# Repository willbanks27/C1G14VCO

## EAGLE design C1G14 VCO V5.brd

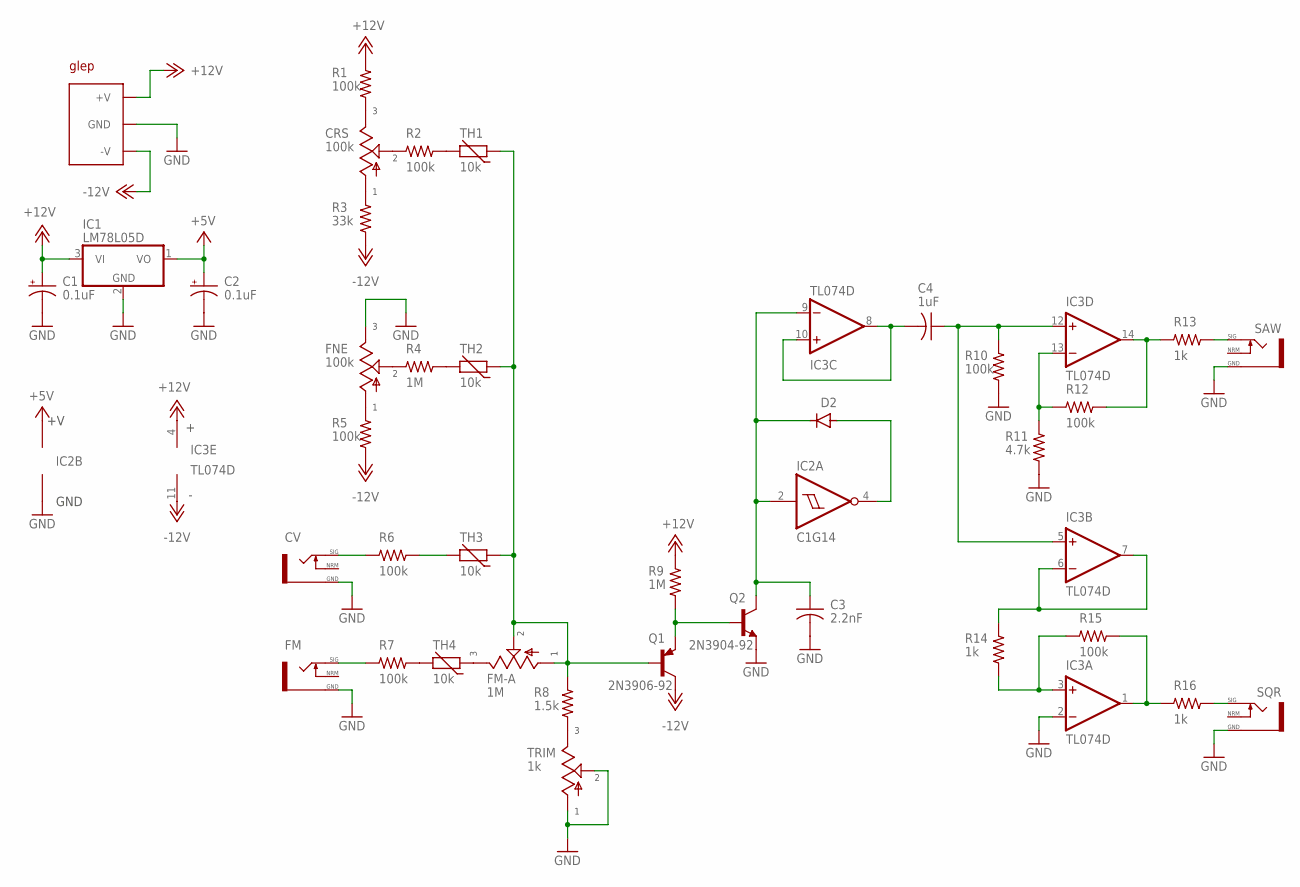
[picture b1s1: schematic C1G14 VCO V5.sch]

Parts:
C1, C2: 0.1uF; E025
C3: 2.2nF; C05
C4: 1uF; C05
CRS: 100k; HEADER
CV: MONOHDR; HEADER
D2: D-123; SOD-123
FM: MONOHDR; HEADER
FM-A: 1M; HEADER
FNE: 100k; HEADER
IC1: LM78L05D; LM78LXX
IC2: C1G14; SOT-23-5
IC3: TL074D; DIL14
Q1: 2N3906-92; TO92
Q2: 2N3904-92; TO92
R1, R2, R5, R6, R7, R10, R12, R15: 100k; R1206
R3: 33k; R1206
R4, R9: 1M; R1206
R8: 1.5k; R1206
R11: 4.7k; R1206
R13, R14, R16: 1k; R1206
SAW: MONOHDR; HEADER
SQR: MONOHDR; HEADER
TH1, TH2, TH3, TH4: 10k; TH025
TRIM: 1k; HEADER
U$1: 10PIN-PWR; 10PIN-HEADER
U$2: GLEP

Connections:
+5V: C2.+, IC1.1 (VO), IC2.5 (V+)
+12V: C1.+, IC1.3 (VI), IC3.4 (V+), R1.2, R9.2, U$1.9 (+V), U$1.10 (+V)
-12V: IC3.11 (V-), Q1.3 (C), R3.1, R5.1, U$1.1 (-V), U$1.2 (-V)
GND: C1.-, C2.-, C3.2, CV.GND (SLEEVE-GND), FM.GND (SLEEVE-GND), FNE.3, IC1.2 (GND), IC2.3 (GND), IC3.2 (INVERTING(-)), Q2.1 (E), R10.1, R11.1, SAW.GND (SLEEVE-GND), SQR.GND (SLEEVE-GND), TRIM.1, TRIM.2, U$1.3 (GND), U$1.4 (GND), U$1.5 (GND), U$1.6 (GND), U$1.7 (GND), U$1.8 (GND)
unnamed: CRS.2, R2.1
unnamed: C4.2, IC3.8 (OUT), IC3.10 (NON-INVERTING(+))
unnamed: CRS.1, R3.2
unnamed: R2.2, TH1.2
unnamed: CRS.3, R1.1
unnamed: FNE.2, R4.1
unnamed: R4.2, TH2.2
unnamed: FNE.1, R5.2
unnamed: IC3.6 (INVERTING(-)), IC3.7 (OUT), R14.2
unnamed: R6.2, TH3.2
unnamed: FM.TIP-SIG, R7.1
unnamed: R7.2, TH4.2
unnamed: FM-A.3, TH4.1
unnamed: R8.1, TRIM.3
unnamed: CV.TIP-SIG, R6.1
unnamed: Q1.1 (E), Q2.2 (B), R9.1
unnamed: C4.1, IC3.5 (NON-INVERTING(+)), IC3.12 (NON-INVERTING(+)), R10.2
unnamed: C3.1, D2.C, IC2.2 (A), IC3.9 (INVERTING(-)), Q2.3 (C)
unnamed: D2.A, IC2.4 (Y)
unnamed: IC3.13 (INVERTING(-)), R11.2, R12.1
unnamed: IC3.14 (OUT), R12.2, R13.1
unnamed: R13.2, SAW.TIP-SIG
unnamed: FM-A.1, FM-A.2, Q1.2 (B), R8.2, TH1.1, TH2.1, TH3.1
unnamed: IC3.3 (NON-INVERTING(+)), R14.1, R15.1
unnamed: IC3.1 (OUT), R15.2, R16.1
unnamed: R16.2, SQR.TIP-SIG

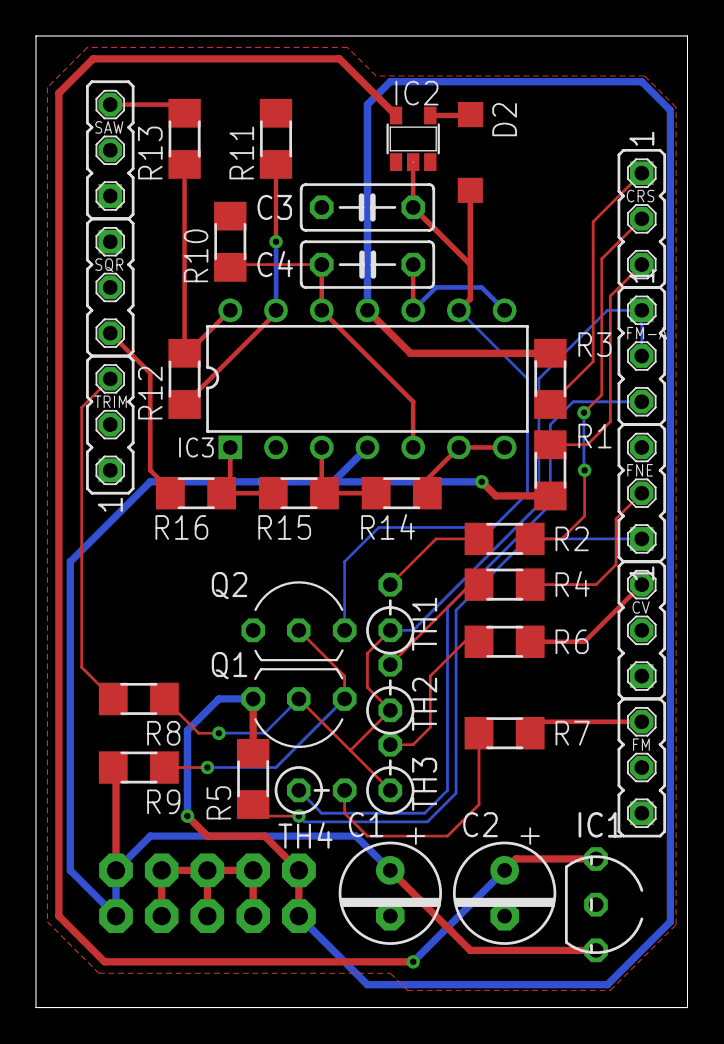
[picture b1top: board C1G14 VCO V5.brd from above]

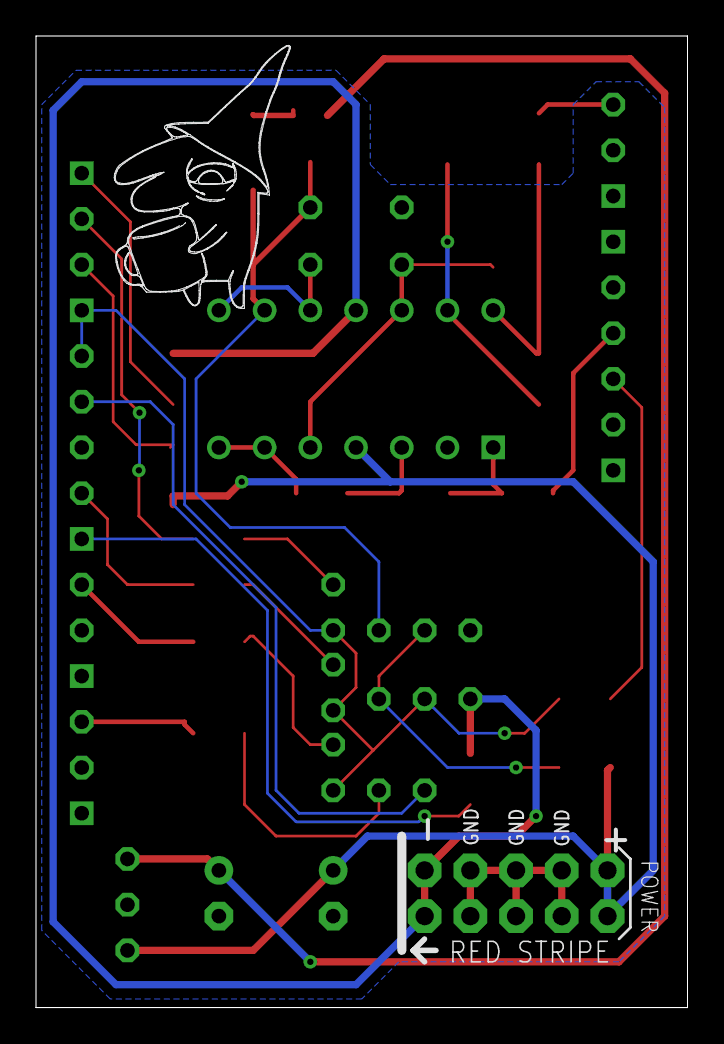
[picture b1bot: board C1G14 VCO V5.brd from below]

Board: 2 copper layers, 36.2 x 54.0 mm, 40 parts (2 on the bottom side), 30 nets.
